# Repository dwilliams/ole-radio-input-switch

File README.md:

ole-radio-input-switch
======================

This project is a collection of schematics and pcb layouts for adding Bluetooth or Line input to an "ole toob" radio.
One key feature of this project is keeping the radio functional, unlike those "strip the chassis and use a cheap
Bluetooth and amplifier" abominations.

Theory of Operation
-------------------

...

Bluetooth Module Data
---------------------

Pinout (Copied from Amazon listing: https://www.amazon.com/gp/product/B07RRW8373):
1. +5V power supply: connect the positive pole of the power supply, the voltage range is 4.2V~5V, please ensure that the
   power supply is within this range. Exceeding this range may damage the module or cause the work to be abnormal.
2. Ground: GND is connected to the negative pole of the power supply.
3. left channel: connect the left channel input of the power amplifier board, or the left channel of the earphone, it is
   recommended to connect a capacitor to the output port (depending on the input matched by the power amplifier).
4. right channel: connect the right channel input of the power amplifier board, or the right channel of the earphone, it
   is recommended to connect a capacitor to the output port (depending on the matching input of the power amplifier).
5. Silent output port: The port is preset to a high level, and the port outputs a low level when muted.
6. Status indicator: When the Bluetooth is not connected, the light flashes quickly, and once the Bluetooth connection
   is successful, it will flash slowly.
7. Reserved port: The port has been pulled up to 5V. When the port is triggered by a low level, it will be turned off.
   When the port is turned back to the low level again.

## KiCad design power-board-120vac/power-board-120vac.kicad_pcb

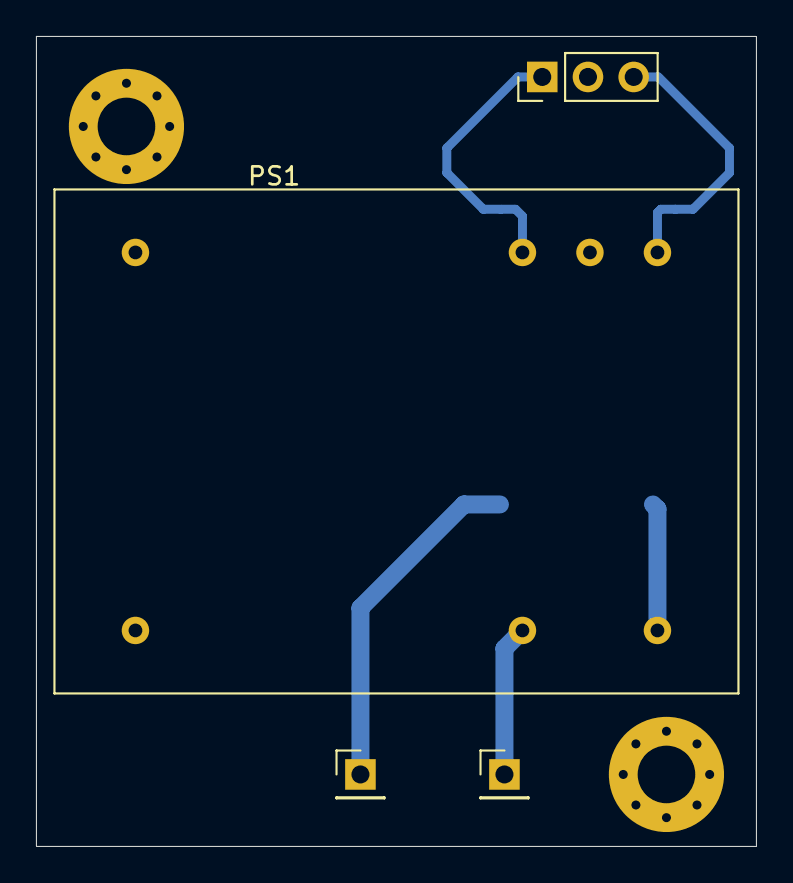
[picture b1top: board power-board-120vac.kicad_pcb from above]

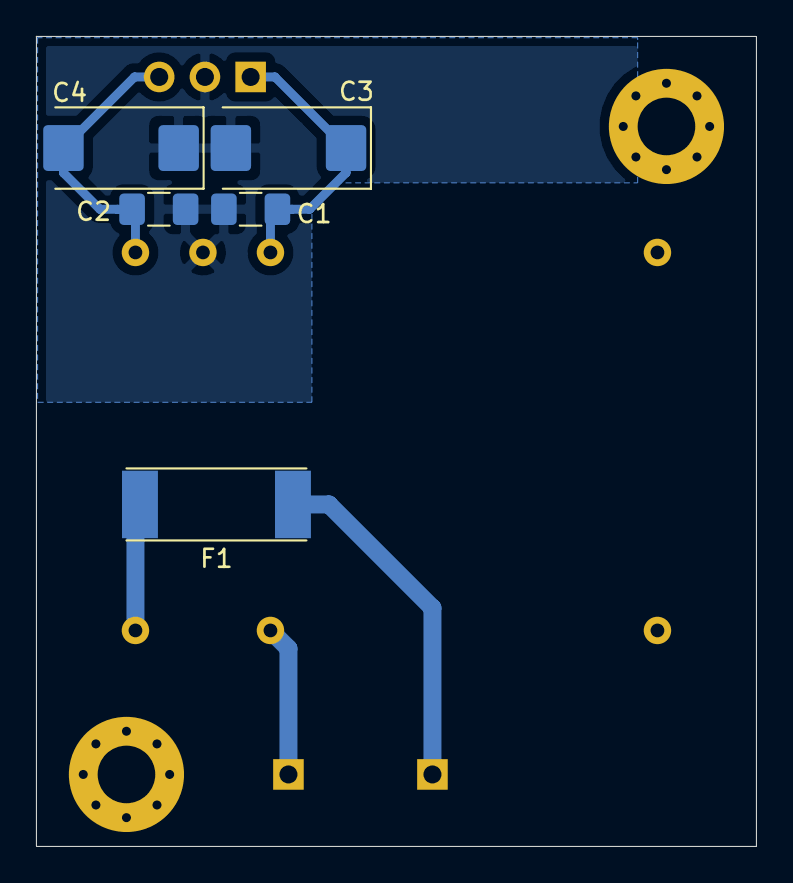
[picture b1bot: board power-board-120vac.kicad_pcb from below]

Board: 2 copper layers, 40.0 x 45.0 mm, 9 parts (5 on the bottom side), 6 nets.

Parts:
C1, C2: 0.1 uF 25 V; C_1206_3216Metric_Pad1.42x1.75mm_HandSolder
C3, C4: 47 uF 25 V; CP_EIA-7343-31_Kemet-D_Pad2.25x2.55mm_HandSolder
F1: Fuse; UMT250
J1, J2: Conn_01x01; PinHeader_1x01_P2.54mm_Vertical
J3: Conn_01x03; PinHeader_1x03_P2.54mm_Vertical
PS1: RAC04

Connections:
GND: C1.2, C2.1, C3.2, C4.1, J3.2, PS1.3
unnamed: C1.1, C3.1, J3.1, PS1.2
unnamed: C2.2, C4.2, J3.3, PS1.4
unnamed: F1.1, PS1.5
unnamed: F1.2, J1.1
unnamed: J2.1, PS1.6

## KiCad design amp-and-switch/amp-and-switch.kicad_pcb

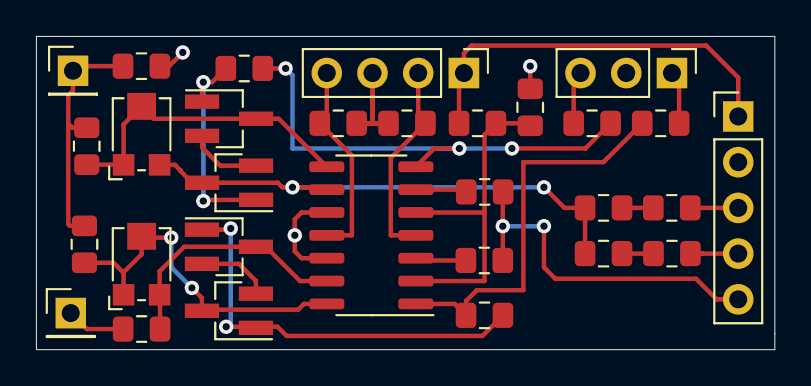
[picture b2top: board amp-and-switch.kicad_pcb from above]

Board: 2 copper layers, 41.0 x 17.4 mm, 30 parts (0 on the bottom side), 26 nets.

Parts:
C1, C2, C3, C4: 100 nF; C_0805_2012Metric_Pad1.15x1.40mm_HandSolder
J1: Conn_01x05; PinHeader_1x05_P2.54mm_Vertical
J2, J5: Conn_01x01; PinHeader_1x01_P2.54mm_Vertical
J3: Conn_01x04; PinHeader_1x04_P2.54mm_Vertical
J4: Conn_01x03; PinHeader_1x03_P2.54mm_Vertical
Q1, Q2, Q3, Q4: Q_NMOS_GSD; SOT-23_Handsoldering
R1, R2, R5, R6, R9, R10, R11: 1K; R_0805_2012Metric_Pad1.15x1.40mm_HandSolder
R7, R8, R16: 20K; R_0805_2012Metric_Pad1.15x1.40mm_HandSolder
R12, R13, R14, R15: 3K; R_0805_2012Metric_Pad1.15x1.40mm_HandSolder
RV1, RV2: 10K; Potentiometer_Bourns_TC33X_Vertical
U1: LM324; SOIC-14_3.9x8.7mm_P1.27mm

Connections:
+2V5: R7.2, R8.1, U1.2, U1.5
+5V: J1.1, J3.1, R7.1
+12V: C1.1, J3.2, U1.4
-12V: C2.2, J3.4, U1.11
/BlueLED: J4.1, R13.1
/BluetoothMute: R9.2, R14.2, U1.7
/RadioMute: R5.2, R13.2, U1.1
/WhiteLED: J4.3, R14.1
GND: C1.2, C2.1, J1.2, J3.3, J4.2, R8.2, R16.2, U1.10, U1.12
unnamed: C3.1, R10.2
unnamed: C3.2, J1.3
unnamed: C4.1, R11.2
unnamed: C4.2, J1.4
unnamed: J1.5, R1.2, R2.2
unnamed: J2.1, R6.2
unnamed: J5.1, R12.1, R15.1, R16.1
unnamed: Q1.1, Q2.1, R5.1
unnamed: Q1.2, Q2.2
unnamed: Q1.3, R12.2, RV1.1, RV1.2, U1.14
unnamed: Q2.3, R6.1, RV1.3, U1.13
unnamed: Q3.1, Q4.1, R9.1
unnamed: Q3.2, Q4.2
unnamed: Q3.3, R15.2, RV2.1, RV2.2, U1.8
unnamed: Q4.3, R10.1, R11.1, RV2.3, U1.9
unnamed: R1.1, U1.3
unnamed: R2.1, U1.6

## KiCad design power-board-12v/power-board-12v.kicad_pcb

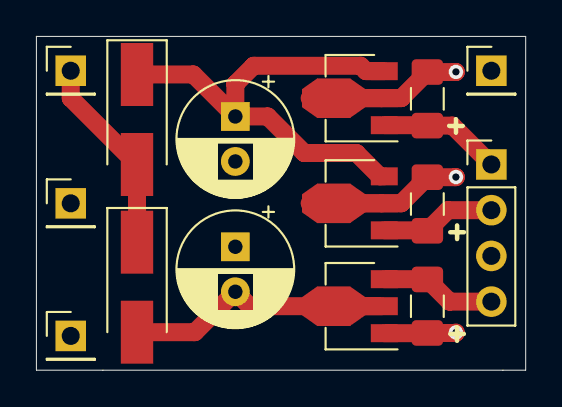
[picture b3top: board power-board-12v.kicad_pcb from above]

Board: 2 copper layers, 27.2 x 18.5 mm, 15 parts (0 on the bottom side), 7 nets.

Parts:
C1, C2: 220 uF; CP_Radial_D6.3mm_P2.50mm
C3, C4, C5: 4.7 uF; C_1206_3216Metric_Pad1.42x1.75mm_HandSolder
D1, D2: D; D_SMA_Handsoldering
J1, J2, J2#2, J2#3: Conn_01x01; PinHeader_1x01_P2.54mm_Vertical
J3: Conn_01x04; PinHeader_1x04_P2.54mm_Vertical
U1: L78L12_SOT89; SOT-89-3
U2: L79L12_SOT89; SOT-89-3
U3: L78L05_SOT89; SOT-89-3

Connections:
GND: C1.2, C2.1, C3.2, C4.1, C5.2, J2.1, J2#2.1, J2#3.1, J3.3, U1.2, U2.1, U3.2
unnamed: C1.1, D1.1, U1.3, U3.3
unnamed: C2.2, D2.2, U2.2
unnamed: C3.1, J3.2, U1.1
unnamed: C4.2, J3.4, U2.3
unnamed: C5.1, J3.1, U3.1
unnamed: D1.2, D2.1, J1.1

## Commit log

2019-09-20 Adding schematic files for one power board and the amp & switch board.
2019-09-20 Page layout and gitignore.
2019-09-21 A bit of the ol' readme and a pin swap.
2019-10-02 Updates to the amp and switch board.
2019-10-02 Updates to and layout of the 12V End Ground Power Board.
2019-10-02 Ignoring gerber folder and fp-info-cache file. The gerbers can be regenerated by plotting again.
2019-10-02 Adding some meta data.
2019-10-10 Fixed a missed ground trace on the switch board.
2019-10-13 Updated both the amp-and-switch board and the power-board-12v board to version 0.2 after performing bring-up and fixing many issues.
2020-10-27 Adding a new power board that takes 120v AC input.
